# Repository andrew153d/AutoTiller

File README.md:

# AutoTiller
An autopilot for my 1977 AMF Sunfish

## Usage ## 
- The AutoTiller attaches to the tiller handle with clips going to each side of the boat.

| Keypress | Action             |
|----------|--------------------|
|  Set     |  sets heading |
|+15|heading+=15|
|-15|heading-=15|
|+1|heaing++|
|-1|heading--|
|Fn & Set| Calibrates compass, rotate device around for 30 seconds|
|Fn & +1| deadspace++|
|Fn & +15| torquePID.P++|
|Fn & -1| deadspace--|
|Fn & -15| torquePID.P-- |

## Schematic

The schematic for the PCB can be found in the `media` directory:

## PCB Layout

The PCB layout file can also be found in the `media` directory:

## PCB Top Layer

The view of the board from the cockpit:

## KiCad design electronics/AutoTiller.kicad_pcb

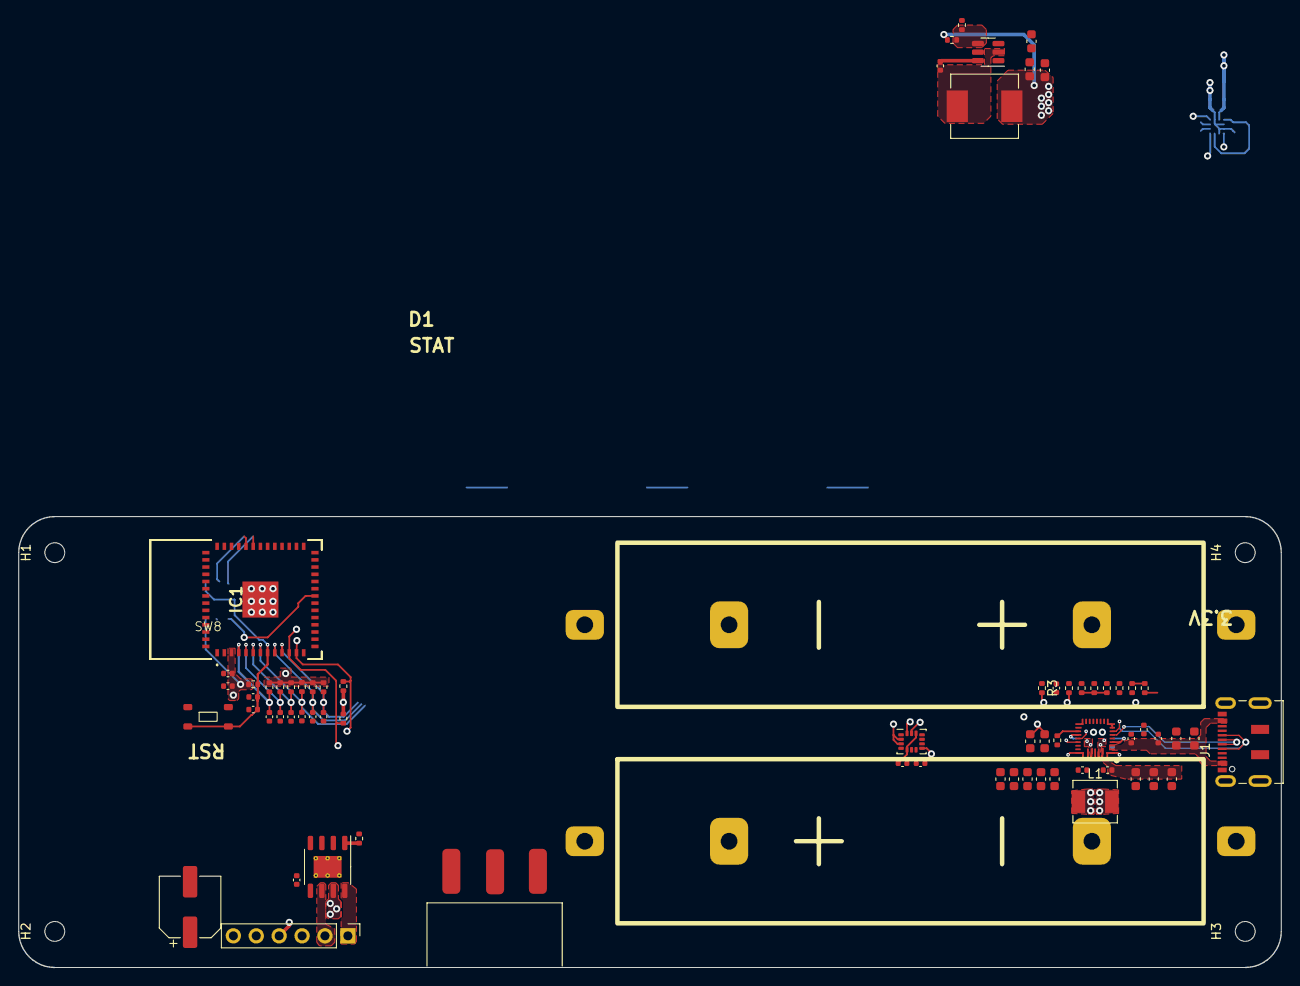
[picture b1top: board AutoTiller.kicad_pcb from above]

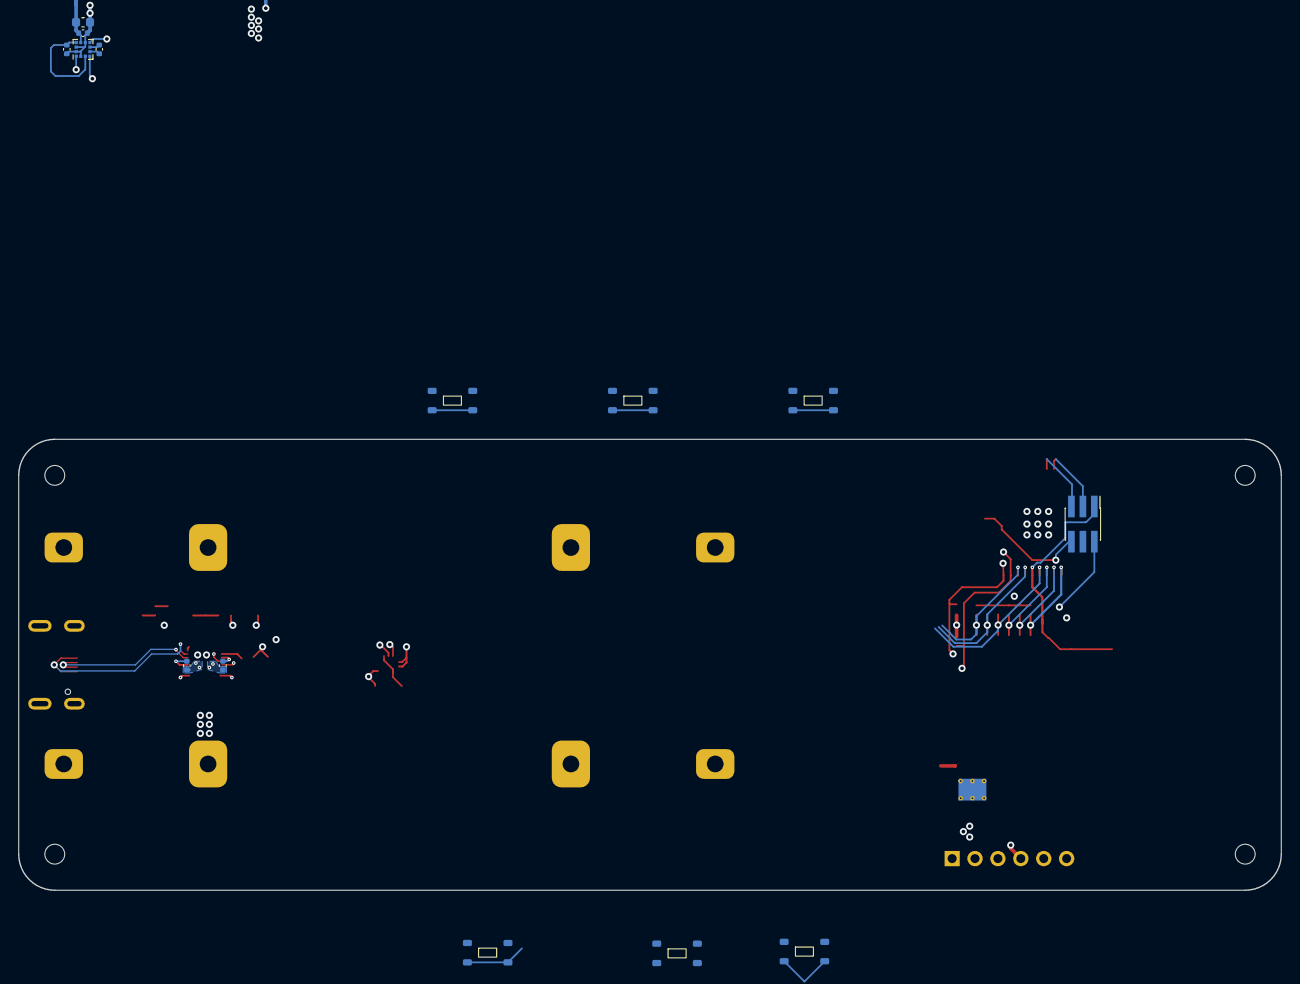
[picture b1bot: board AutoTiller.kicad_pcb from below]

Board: 4 copper layers, 140.0 x 50.0 mm, 88 parts (14 on the bottom side), 55 nets.

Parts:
BQ25792RQMR1: BQ25792
BT1, BT2: Battery; 254 clip
C1, C2, C3, C9, C10, C11, C12, C15, C20, C21, C29, C34, C37, C38, C39: 0.1u; C_0402_1005Metric
C4, C5, C8, C16, C19, C22, C23, C24, C25, C27, C28, C30, C33, C41: 10u; C_0603_1608Metric
C6, C7: 47n; C_0402_1005Metric
C13: .1u; C_0402_1005Metric
C14, C18: 22u; C_0603_1608Metric
C17: 4.7u; C_0402_1005Metric
C26: 22u; C_0402_1005Metric
C31: 1n; C_0402_1005Metric
C32: 1u; C_0402_1005Metric
C35, C42: 100n; C_0402_1005Metric
C36: 0.22u; C_0402_1005Metric
C40: 47u; CP_Elec_6.3x5.9
DRV8251ADDAR1: HSOP-8-1EP_3.9x4.9mm_P1.27mm_EP2.41x3.1mm_ThermalVias
H1, H2, H3, H4: MountingHole; MountingHole_2.2mm_M2
IC1: ESP32-C3-MINI-1-N4; ESP32MINI1N4
J1: USB_C_Receptacle_USB2.0; USB_C_Receptacle_JAE_DX07S016JA1R1500
J2: UART; PinHeader_2x03_P1.27mm_Vertical_SMD
L1: 1u; L_Sunlord_MWSA0402S
L2: 3.3u; L_Sunlord_MWSA0618S
LSM6DSMTR1: LGA-14_3x2.5mm_P0.5mm_LayoutBorder3x4y
R1, R4, R5, R6, R9, R15: 47k; R_0402_1005Metric
R2, R3, R8, R14, R18, R24, R25: 10k; R_0402_1005Metric
R7: 31.6k; R_0402_1005Metric
R10: 100; R_0402_1005Metric
R11: 5.24k; R_0402_1005Metric
R12: 30.31k; R_0402_1005Metric
R13: 127k; R_0402_1005Metric
R16: 6.04k; R_0402_1005Metric
R17: 100k; R_0402_1005Metric
R26: 5.1k; R_0402_1005Metric
SW1: +1; Tactile_5.5mmx2.85mm
SW2: -1; Tactile_5.5mmx2.85mm
SW3: +15; Tactile_5.5mmx2.85mm
SW4: -15; Tactile_5.5mmx2.85mm
SW5: Power; 0.5in_Slide
SW6: L; Tactile_5.5mmx2.85mm
SW7: R; Tactile_5.5mmx2.85mm
SW8: Reset; Tactile_5.5mmx2.85mm
U1: TSOT-23-6
U2: LGA-12_2x2mm_P0.5mm
U3: PinHeader_1x06_P2.54mm_Vertical

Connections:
+1: C2.1, IC1.6 (I38), R1.2, SW1.2
+3.3V: C14.1, C18.1, C26.1, C29.1, C35.1, C39.1, C41.1, IC1.3 (3V3), J2.2, L2.2, LSM6DSMTR1.8 (VDD), R1.1, R4.1, R5.1, R6.1, R7.1, R9.1, R15.1, R18.1, R24.1, R25.1, U2.9 (Vdd), U3.4 (ENC_VCC)
+12V: BQ25792RQMR1.25 (SYS), C4.1, C21.1, C23.1, C24.1, C27.1, C30.1, C33.1, U1.3 (VIN)
+15: C10.1, IC1.5 (I37), R5.2, SW3.2
-1: C9.1, IC1.7 (I39), R4.2, SW2.2
-15: C12.1, IC1.9 (I34), R6.2, SW4.2
/BATP: BQ25792RQMR1.18 (BATP), R10.1
/BST: C11.1, U1.6 (BST)
/BT1: BT1.2 (-), BT2.1 (+)
/BTST1: BQ25792RQMR1.4 (BTST1), C6.1
/BTST2: BQ25792RQMR1.19 (BTST2), C7.2
/CE: BQ25792RQMR1.13 (CE), R2.2
/FB: R7.2, R8.1, U1.4 (FB)
/ILIM_HIZ: BQ25792RQMR1.17 (ILIM_HIZ), R13.1, R17.1
/INT: BQ25792RQMR1.21 (INT), R3.2
/OUT1: DRV8251ADDAR1.8 (OUT1), U3.1 (MVCC)
/OUT2: DRV8251ADDAR1.6 (OUT2), U3.2 (MGND)
/PMID: BQ25792RQMR1.29 (PMID), C13.1, C16.1, C19.1, C22.1
/PROG: BQ25792RQMR1.20 (PROG), R16.1
/SDRV: BQ25792RQMR1.24 (SDRV), C31.1
/SW: C11.2, L2.1, U1.2 (SW)
/SW1: BQ25792RQMR1.28 (SW1), C6.2, L1.2
/SW2: BQ25792RQMR1.26 (SW2), C7.1, L1.1
/TS: BQ25792RQMR1.16 (TS), R11.2, R12.1, R14.1
/VAC: BQ25792RQMR1.8 (VAC2), BQ25792RQMR1.9 (VAC1)
BC_INT: IC1.18 (IO13), R3.1
BT2: BT2.2 (-), SW5.3 (C)
Compass_INT: IC1.13 (IO25), U2.7 (INT)
D+: BQ25792RQMR1.6 (D+), J1.A6 (D+), J1.B6 (D+)
D-: BQ25792RQMR1.7 (D-), J1.A7 (D-), J1.B7 (D-)
ENC_A: IC1.25 (IO9), U3.5 (ENC_A)
ENC_B: IC1.26 (IO10), U3.6 (ENC_B)
ESP_EN: C32.1, C34.1, IC1.8 (EN), J2.1, R18.2, SW8.2
ESP_IO0: IC1.21 (IO0), J2.6
ESP_RXD: IC1.35 (RXD0), J2.5
ESP_TXD: IC1.36 (TXD0), J2.3
GND: BQ25792RQMR1.10 (ACDRV2), BQ25792RQMR1.11 (ACDRV1), BQ25792RQMR1.27 (GND), C1.2, C2.2, C3.2, C4.2, C5.2, C8.2, C9.2, C10.2, C12.2, C13.2, C14.2, C15.2, C16.2, C17.2, C18.2, C19.2, C20.2, C21.2, C22.2, C23.2, C24.2, C25.2, C26.2, C27.2, C28.2, C29.2, C30.2, C31.2, C32.2, C33.2, C34.2, C35.2, C36.2, C37.2, C38.2, C39.2, C40.2, C41.2, C42.2, DRV8251ADDAR1.7 (GND), DRV8251ADDAR1.9 (PAD), IC1.1 (GND_1), IC1.2 (GND_2), IC1.27 (GND), IC1.38 (GND), IC1.39 (GND), IC1.40 (GND), IC1.41 (GND), IC1.42 (GND), IC1.43 (GND), IC1.44 (GND), IC1.45 (GND), IC1.46 (GND), IC1.47 (GND), IC1.48 (GND), IC1.49 (GND), IC1.50 (GND), IC1.51 (GND), IC1.52 (GND), IC1.53 (GND), IC1.54 (GND), IC1.55 (GND), J1.A1 (GND), J1.A12 (GND), J1.B1 (GND), J1.B12 (GND), J2.4, LSM6DSMTR1.2 (SDx), LSM6DSMTR1.3 (SCx), LSM6DSMTR1.6 (GND), LSM6DSMTR1.7 (GND), R2.1, R8.2, R12.2, R14.2, R16.2, R17.2, R26.1, SW1.1, SW2.1, SW3.1, SW4.1, SW5.2 (B), SW6.1, SW7.1, SW8.1, U1.1 (GND), U2.2 (NC), U2.6 (GND), U2.8 (GND), U2.11 (NC), U2.12 (NC), U3.3 (ENC_GND)
IMU_INT1: IC1.32 (IO19), LSM6DSMTR1.4 (INT1)
IMU_INT2: IC1.34 (IO21), LSM6DSMTR1.9 (INT2)
MC_IN1: DRV8251ADDAR1.3 (IN1), IC1.30 (IO18)
MC_IN2: DRV8251ADDAR1.2 (IN2), IC1.31 (IO23)
MC_VREF: DRV8251ADDAR1.4 (VREF), IC1.29 (IO5)
unnamed: DRV8251ADDAR1.1 (IPROPI), R26.2
unnamed: C42.1, LSM6DSMTR1.5 (VDDIO), LSM6DSMTR1.12 (CS)
unnamed: C36.1, U2.5 (C1)
QON: BQ25792RQMR1.12 (nQON), IC1.16 (IO14)
REGN: BQ25792RQMR1.5 (REGN), C17.1, R11.1, R13.2
SAO: IC1.33 (IO22), LSM6DSMTR1.1 (SA0)
SCL: BQ25792RQMR1.14 (SCL), IC1.12 (IO33), LSM6DSMTR1.13 (SCL), R24.2, U2.1 (SCL)
SDA: BQ25792RQMR1.15 (SDA), IC1.11 (IO32), LSM6DSMTR1.14 (SDA), R25.2, U2.4 (SDA)
TackL: C15.1, IC1.10 (I35), R9.2, SW6.2
TackR: C20.1, IC1.4 (I36), R15.2, SW7.2
VBAT: BQ25792RQMR1.22 (BAT), BQ25792RQMR1.23 (BAT), BT1.1 (+), C25.1, C28.1, C38.1, C40.1, DRV8251ADDAR1.5 (VM), R10.2
VBUS: BQ25792RQMR1.2 (VBUS), BQ25792RQMR1.3 (VBUS), C1.1, C3.1, C5.1, C8.1, J1.A4 (VBUS), J1.A9 (VBUS), J1.B4 (VBUS), J1.B9 (VBUS)
Vdd_IO: C37.1, U2.3 (CS), U2.10 (Vdd-IO)

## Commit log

2023-05-08 Add README
2023-05-08 Restructure and add README
2023-05-08 add images to README
2023-05-08 add pcb view
2023-05-23 OTA working
2023-05-29 Final Rev2 PCB
2023-06-08 update main to search addresses and add images
2023-06-23 Simple PID controller working
2023-06-27 cleaned and reformatted
2023-06-27 working simple pwm and inturrupt
2023-06-27 working inturrupts and pwm within motor class
2023-06-27 Successful Angle Readout
2023-06-27 add light flashing for battery level output
2023-06-28 tiller control refined, needs tuning
2023-07-02 allow charger to flash battery level
2023-07-07 update compass setup
2023-07-08 use platformio compass library and setup default offsets
2023-08-13 update for new form factor
2023-08-21 simplify for new layout
2023-12-19 stash
